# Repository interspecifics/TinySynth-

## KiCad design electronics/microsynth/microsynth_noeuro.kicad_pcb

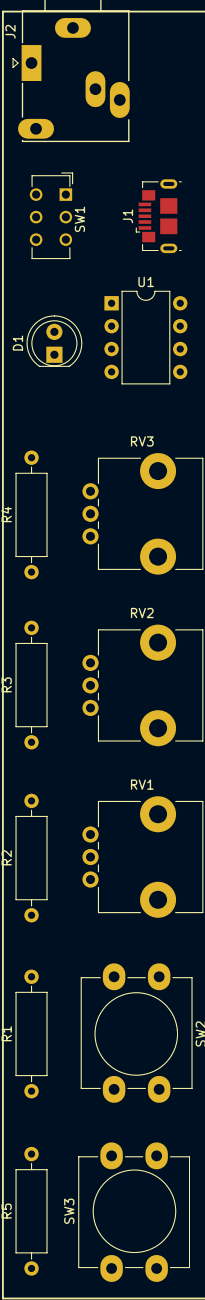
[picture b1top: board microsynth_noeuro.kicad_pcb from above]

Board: 2 copper layers, 15 parts (0 on the bottom side), 12 nets, no tracks yet.

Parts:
D1: LED; LED_D5.0mm_FlatTop
J1: USB_B_Micro; USB_Micro-B_GCT_USB3076-30-A
J2: AudioJack3_Ground; StereoJack_3.5mm_Switch_Ledino_KB3SPRS_Horizontal_TRS
R1, R2, R5: 47K; R_Axial_DIN0309_L9.0mm_D3.2mm_P12.70mm_Horizontal
R3: 2.2K; R_Axial_DIN0309_L9.0mm_D3.2mm_P12.70mm_Horizontal
R4: 4.7K; R_Axial_DIN0309_L9.0mm_D3.2mm_P12.70mm_Horizontal
RV1, RV2, RV3: 10K; Potentiometer_Alps_RK09L_Single_Vertical
SW1: SW_SPDT; SW_CuK_JS202011CQN_DPDT_Straight
SW2, SW3: SW_Push; SW_PUSH-12mm_Wuerth-430476085716
U1: ATtiny85-20PU; DIP-8_W7.62mm

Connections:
GND: D1.1, J1.5, J1.6, J2.S, R2.2, R4.2, RV1.3, RV2.3, RV3.3, U1.4
unnamed: J1.1, SW1.3
unnamed: J2.R, J2.T, R3.2, R4.1
unnamed: R2.1, SW2.1
unnamed: R5.1, SW3.1
unnamed: RV1.2, U1.3
unnamed: RV2.2, U1.2
unnamed: RV3.2, U1.7
P1: R1.2, SW2.2, SW3.2, U1.1
P5: D1.2, R3.1, U1.5
P6: R5.2, U1.6
V_IN: R1.1, RV1.1, RV2.1, RV3.1, SW1.2, U1.8

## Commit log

2019-05-15 kicad files
2019-05-15 code nsample
